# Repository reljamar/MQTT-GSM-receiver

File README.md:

# MQTT-GSM-receiver
_A basic IoT device that connects to a mobile network and activates an output pin based on an MQTT message. The project is a work in progress_

## Purpose
This project is intended to be a basis of operation for a vast number of possible uses. The microcontroller connects to an MQTT topic and checks for key messages. When the appropriate message is received, an output pin is activated. With aditional periferal hardware, the device can be adapted to do various tasks. An important detail about the project is that unlike most IoT devices that connect via WiFi, this one connects via the mobile network, allowing it to be placed outside the range of WiFi networks: backyards, open fields, practically anywhere. The project also serves to prived an introduction to RF connectivity.

## Description
A device that uses the STM32L476RET6 microcontroller. The microcontroller communicates with a Quectel BC660K-GL GSM module using AT commands. The device subsribes to a topic on a server set up by the user, and an mobile phone application can send messages to that topic, which trigger the IoT device to activate an output signal. The device features a SIM card, EEPROM, and an input/ouput interface. Cybersecurity is of crucial importance for this application, however it is far from being developed at the time of writing. Currently an external antenna is used, but future iterations may include a built-in PCB antenna.

## Overview
- Quectel CB660K-GL GMS module for connectivity
- EEPROM for cybersecurity credentials
- Basis for projects with a well-defined use case

## System architecture
### Microcontroller
The system is based on an STM32L476RET6. They are readily available and powerful enough for encryption tasks. The microcontroller communicates vie UART using AT commands with the GSM module
### GSM Module
The module is Quectel's BC660K-GL. This is one of the cheapest GMS modules available, and even they are sometimes difficult to get by. The module is very easy to use with the AT commands, which makes development much faster. An important note is the antenna design, which is currently a weak spot in the project. Occasionally, the device simply loses its connection with the network. The module requires a SIM card. Some carriers offer IoT-specific services, which come with only data at a very slow rate, but are also very cheap on a monthly level.
### Antenna
The antenna is the weak link, and much care is needed when routing the antenna signal, even if an external antenna is used. Impedance control is very important here.

## Firmware
### Implemented features
- [x] Connecting to a GSM network
- [x] Subscribing to a topic
- [x] Error handling - lost connection triggers a reconnection attempt
- [x] Output pin control based on MQTT messages
### Planned features
- [ ] Cybersecurity
- [ ] Reporting/check-in feature
- [ ] Sending data from the input to the server

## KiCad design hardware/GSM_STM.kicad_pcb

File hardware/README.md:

This folder contains all of the hardware project files.
There is only one schematic page containing all the functions.
A BOM is attached since the antenna is not visible in the PCB project.

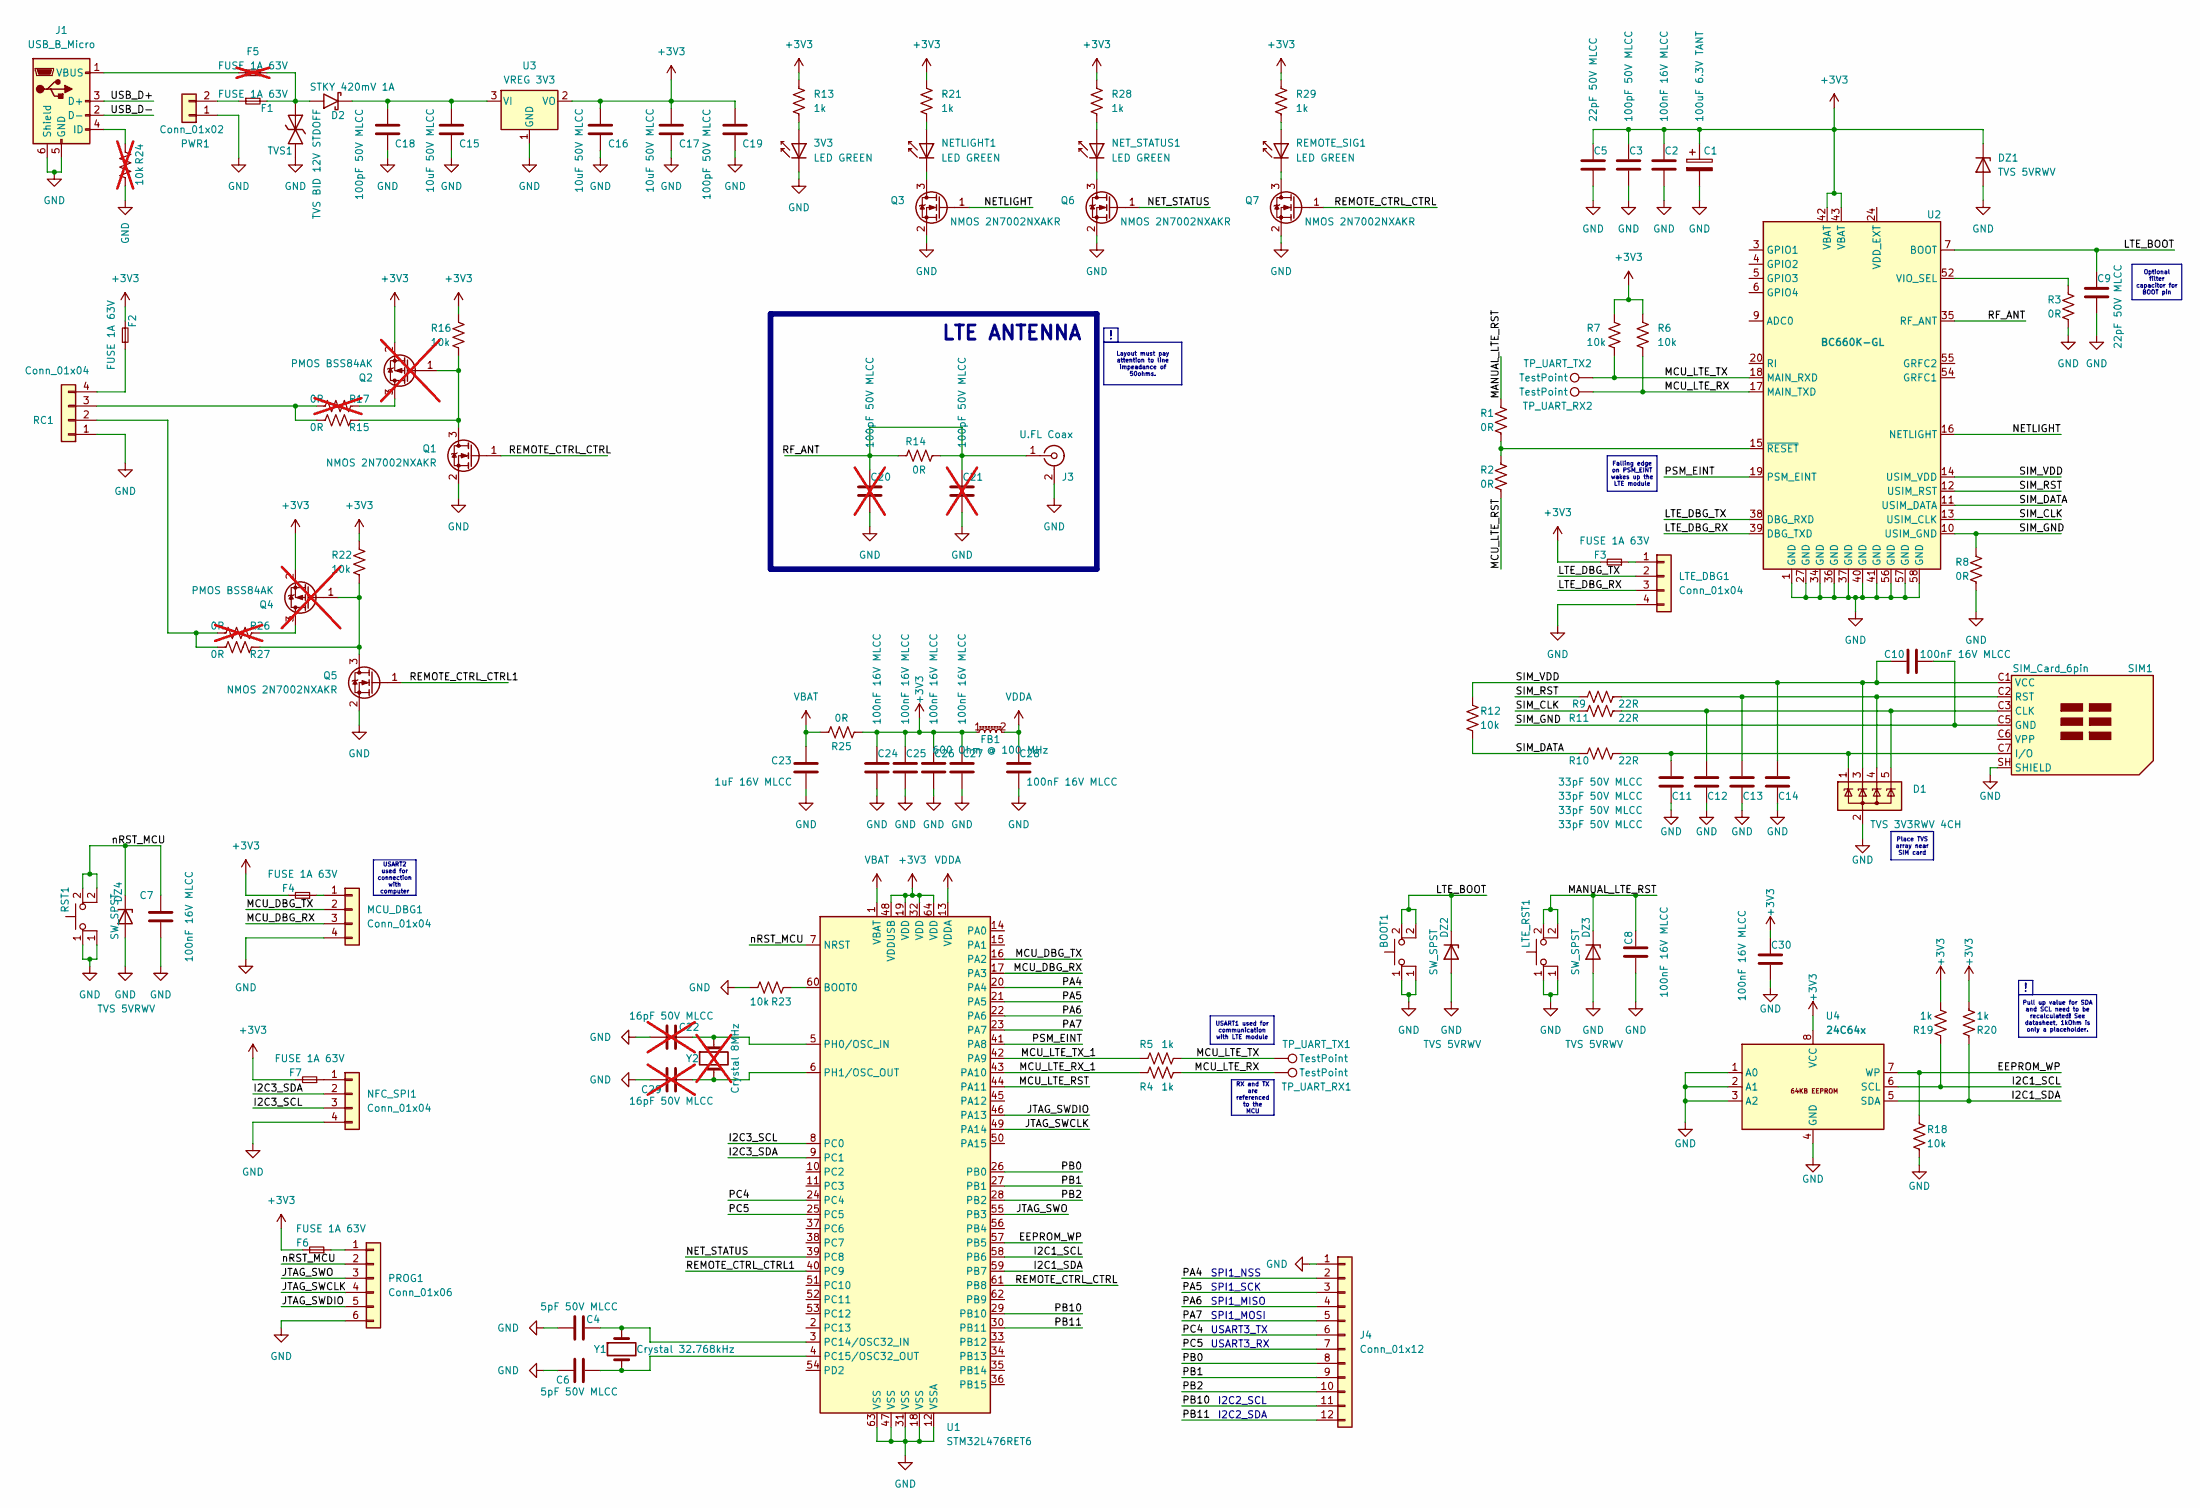
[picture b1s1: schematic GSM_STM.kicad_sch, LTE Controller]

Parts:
3V3: LED GREEN; LED_0603_1608Metric; Forward Voltage 2V; Manufacturer Part Number 150060VS75000
BOOT1: SW_SPST; SW_SPST_PTS645; Contact Rating 50mA @ 12V; Manufacturer Part Number PTS645SL43SMTR92 LFS
C1: 100uF 6.3V TANT; CP_EIA-3528-15_AVX-H; Tolerance 10%; Rated Voltage 6.3V; Manufacturer Part Number TPSB107K006R0250
C2, C7, C8, C10, C24, C25, C26, C27, C28, C30: 100nF 16V MLCC; C_0603_1608Metric; Tolerance 10%; Rated Voltage 16V; Manufacturer Part Number CL10B104KO8NNNC
C3, C18, C19: 100pF 50V MLCC; C_0603_1608Metric; Tolerance 5%; Rated Voltage 50V; Manufacturer Part Number CC0603JRNPO9BN101
C4, C6: 5pF 50V MLCC; C_0402_1005Metric; Tolerance ±0.1pF; Rated Voltage 50V; Manufacturer Part Number CC0402BRNPO9BN5R0
C5, C9: 22pF 50V MLCC; C_0603_1608Metric; Tolerance 5%; Rated Voltage 50V; Manufacturer Part Number CC0603JRNPO9BN220
C11, C12, C13, C14: 33pF 50V MLCC; C_0603_1608Metric; Tolerance 5%; Rated Voltage 50V; Manufacturer Part Number CL10C330JB8NNNC
C15, C16, C17: 10uF 50V MLCC; C_1206_3216Metric; Tolerance 10%; Rated Voltage 50V; Manufacturer Part Number CL31B106KBHNNNE
C20, C21: 100pF 50V MLCC; C_0603_1608Metric; Tolerance 5%; Rated Voltage 50V; Manufacturer Part Number CC0603JRNPO9BN101; not fitted
C22, C29: 16pF 50V MLCC; C_0402_1005Metric; Tolerance ±1%; Rated Voltage 50V; Manufacturer Part Number GJM1555C1H160FB01J; not fitted
C23: 1uF 16V MLCC; C_0603_1608Metric; Tolerance 10%; Rated Voltage 16V; Manufacturer Part Number CC0603KRX7R7BB105
D1: TVS 3V3RWV 4CH; SOT-665; Clamping Voltage 12V @ Ipp = 3A; Manufacturer Part Number PESD3V3L4UW
D2: STKY 420mV 1A; D_SMA; Forward Voltage 420mV @ 1A; Manufacturer Part Number SS12L_R1_00001
DZ1, DZ2, DZ3, DZ4: TVS 5VRWV; D_SOD-923; Clamping Voltage 12.3V; Manufacturer Part Number ESD9X5.0ST5G
F1, F2, F3, F4, F6, F7: FUSE 1A 63V; Fuse_1206_3216Metric; Current Rating 1A; Voltage Rating 63V; Manufacturer Part Number 0685T1000-01
F5: FUSE 1A 63V; Fuse_1206_3216Metric; Current Rating 1A; Voltage Rating 63V; Manufacturer Part Number 0685T1000-01; not fitted
FB1: 600 Ohm @ 100 MHz; L_0603_1608Metric; Current Rating (Max) 300mA; Manufacturer Part Number BBBK00160808601Y00
J1: USB_B_Micro; USB_Micro-B_Amphenol_10118194_Horizontal; Manufacturer Part Number 10118194-0001LF
J3: U.FL Coax; U.FL_Molex_MCRF_73412-0110_Vertical; Manufacturer Part Number CONMHF1-SMD-T
J4: Conn_01x12; PinHeader_1x12_P2.54mm_Vertical
LTE_DBG1: Conn_01x04; Molex_KK-254_AE-6410-04A_1x04_P2.54mm_Vertical
LTE_RST1: SW_SPST; SW_SPST_PTS645; Contact Rating 50mA @ 12V; Manufacturer Part Number PTS645SL43SMTR92 LFS
MCU_DBG1: Conn_01x04; Molex_KK-254_AE-6410-04A_1x04_P2.54mm_Vertical
NETLIGHT1: LED GREEN; LED_0603_1608Metric; Forward Voltage 2V; Manufacturer Part Number 150060VS75000
NET_STATUS1: LED GREEN; LED_0603_1608Metric; Forward Voltage 2V; Manufacturer Part Number 150060VS75000
NFC_SPI1: Conn_01x04; Molex_KK-254_AE-6410-04A_1x04_P2.54mm_Vertical
PROG1: Conn_01x06; Molex_KK-254_AE-6410-06A_1x06_P2.54mm_Vertical
PWR1: Conn_01x02; Molex_KK-254_AE-6410-02A_1x02_P2.54mm_Vertical
Q1, Q3, Q5, Q6, Q7: NMOS 2N7002NXAKR; SOT-23-3; Manufacturer Part Number 2N7002NXAKR
Q2, Q4: PMOS BSS84AK; SOT-23-3; Manufacturer Part Number BSS84AK; not fitted
R1, R2, R3, R8, R14, R15, R25, R27: 0R; R_0603_1608Metric; Tolerance Jumper; Power Rating 100mW; Manufacturer Part Number ERJ-3GEY0R00V
R4, R5, R13, R19, R20, R21, R28, R29: 1k; R_0603_1608Metric; Tolerance 1%; Power Rating 100mW; Manufacturer Part Number ERJ-3EKF1001V
R6, R7, R12, R16, R18, R22, R23: 10k; R_0603_1608Metric; Tolerance 1%; Power Rating 100mW; Manufacturer Part Number ERJ-3EKF1002V
R9, R10, R11: 22R; R_0603_1608Metric; Tolerance 1%; Power Rating 100mW; Manufacturer Part Number RC0603FR-0722RL
R17, R26: 0R; R_0603_1608Metric; Tolerance Jumper; Power Rating 100mW; Manufacturer Part Number ERJ-3GEY0R00V; not fitted
R24: 10k; R_0603_1608Metric; Tolerance 1%; Power Rating 100mW; Manufacturer Part Number ERJ-3EKF1002V; not fitted
RC1: Conn_01x04; Molex_KK-254_AE-6410-04A_1x04_P2.54mm_Vertical
REMOTE_SIG1: LED GREEN; LED_0603_1608Metric; Forward Voltage 2V; Manufacturer Part Number 150060VS75000
RST1: SW_SPST; SW_SPST_PTS645; Contact Rating 50mA @ 12V; Manufacturer Part Number PTS645SL43SMTR92 LFS
SIM1: SIM_Card_6pin; CUI_MICRO_SIM; Manufacturer Part Number MSIM-10-B
TP_UART_RX1, TP_UART_RX2: TestPoint; TestPoint_Pad_1.0x1.0mm
TP_UART_TX1, TP_UART_TX2: TestPoint; TestPoint_Pad_1.0x1.0mm
TVS1: TVS BID 12V STDOFF; D_SMB; Breakdown Voltage 13.3V; Clamping Voltage 19V; Manufacturer Part Number P6SMBJ12CA_R1_00001
U1: STM32L476RET6; LQFP-64_10x10mm_P0.5mm; Manufacturer Part Number STM32L476RET6TR
U2: BC660K-GL; Quectel_BC66; Manufacturer Part Number BC660K-GL
U3: VREG 3V3; SOT-223-3_TabPin2; Output Voltage 3.3V; Dropout Voltage 1.2V; Manufacturer Part Number AZ1117IH-3.3TRG1
U4: 24C64x; SOIC-8_3.9x4.9mm_P1.27mm; Manufacturer Part Number AT24C64D-SSHM-T
Y1: Crystal 32.768kHz; Crystal_C38-LF_D3.0mm_L8.0mm_Horizontal; Frequency Tolerance ±20ppm; Manufacturer Part Number 32.768K12.5P2/DT38
Y2: Crystal 8MHz; Crystal_SMD_HC49-SD; Frequency Tolerance ±30ppm; Manufacturer Part Number ATS080BSM-1E; not fitted

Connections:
+3V3: C1.1, C2.1, C3.1, C5.1, C16.1, C17.1, C19.2, C24.1, C25.1, C26.1, C27.1, C30.1, DZ1.1 (K), F2.2, F3.2, F4.2, F6.2, F7.2, FB1.1, Q2.2 (S), Q4.2 (S), R6.1, R7.1, R13.1, R16.1, R19.1, R20.1, R21.1, R22.1, R25.2, R28.1, R29.1, U1.19 (VDD), U1.32 (VDD), U1.48 (VDDUSB), U1.64 (VDD), U2.42 (VBAT), U2.43 (VBAT), U3.2 (VO), U4.8 (VCC)
/EEPROM_WP: R18.1, U1.57 (PB5), U4.7 (WP)
/I2C1_SCL: R19.2, U1.58 (PB6), U4.6 (SCL)
/I2C1_SDA: R20.2, U1.59 (PB7), U4.5 (SDA)
/I2C3_SCL: NFC_SPI1.3, U1.8 (PC0)
/I2C3_SDA: NFC_SPI1.2, U1.9 (PC1)
/JTAG_SWCLK: PROG1.4, U1.49 (PA14)
/JTAG_SWDIO: PROG1.5, U1.46 (PA13)
/JTAG_SWO: PROG1.3, U1.55 (PB3)
/LTE_BOOT: BOOT1.2, C9.1, DZ2.1 (K), U2.7 (BOOT)
/LTE_DBG_RX: LTE_DBG1.3, U2.39 (DBG_TXD)
/LTE_DBG_TX: LTE_DBG1.2, U2.38 (DBG_RXD)
/MANUAL_LTE_RST: C8.2, DZ3.1 (K), LTE_RST1.2, R1.1
/MCU_DBG_RX: MCU_DBG1.3, U1.17 (PA3)
/MCU_DBG_TX: MCU_DBG1.2, U1.16 (PA2)
/MCU_LTE_RST: R2.2, U1.44 (PA11)
/MCU_LTE_RX: R4.1, R6.2, TP_UART_RX1.1, TP_UART_RX2.1, U2.17 (MAIN_TXD)
/MCU_LTE_RX_1: R4.2, U1.43 (PA10)
/MCU_LTE_TX: R5.1, R7.2, TP_UART_TX1.1, TP_UART_TX2.1, U2.18 (MAIN_RXD)
/MCU_LTE_TX_1: R5.2, U1.42 (PA9)
/NETLIGHT: Q3.1 (G), U2.16 (NETLIGHT)
/NET_STATUS: Q6.1 (G), U1.39 (PC8)
/PA4: J4.2, U1.20 (PA4)
/PA5: J4.3, U1.21 (PA5)
/PA6: J4.4, U1.22 (PA6)
/PA7: J4.5, U1.23 (PA7)
/PB0: J4.8, U1.26 (PB0)
/PB1: J4.9, U1.27 (PB1)
/PB2: J4.10, U1.28 (PB2)
/PB10: J4.11, U1.29 (PB10)
/PB11: J4.12, U1.30 (PB11)
/PC4: J4.6, U1.24 (PC4)
/PC5: J4.7, U1.25 (PC5)
/PSM_EINT: U1.41 (PA8), U2.19 (PSM_EINT)
/REMOTE_CTRL_CTRL: Q1.1 (G), Q7.1 (G), U1.61 (PB8)
/REMOTE_CTRL_CTRL1: Q5.1 (G), U1.40 (PC9)
/RF_ANT: C20.1, C21.1, J3.1 (In), R14.1, R14.2, U2.35 (RF_ANT)
/SIM_CLK: R11.1, U2.13 (USIM_CLK)
/SIM_DATA: R10.1, R12.2, U2.11 (USIM_DATA)
/SIM_GND: C10.2, R8.1, SIM1.C5 (GND), U2.10 (USIM_GND)
/SIM_RST: R9.1, U2.12 (USIM_RST)
/SIM_VDD: C10.1, C14.1, D1.3 (K), R12.1, SIM1.C1 (VCC), U2.14 (USIM_VDD)
/USB_D+: J1.3 (D+)
/USB_D-: J1.2 (D-)
/nRST_MCU: C7.2, DZ4.1 (K), PROG1.2, RST1.2, U1.7 (NRST)
GND: 3V3.1 (K), BOOT1.1, C1.2, C2.2, C3.2, C4.1, C5.2, C6.1, C7.1, C8.1, C9.2, C11.2, C12.2, C13.2, C14.2, C15.2, C16.2, C17.2, C18.1, C19.1, C20.2, C21.2, C22.1, C23.2, C24.2, C25.2, C26.2, C27.2, C28.2, C29.1, C30.2, D1.2 (A), DZ1.2 (A), DZ2.2 (A), DZ3.2 (A), DZ4.2 (A), J1.5 (GND), J1.6 (Shield), J3.2 (Ext), J4.1, LTE_DBG1.4, LTE_RST1.1, MCU_DBG1.4, NFC_SPI1.4, PROG1.6, PWR1.1, Q1.2 (S), Q3.2 (S), Q5.2 (S), Q6.2 (S), Q7.2 (S), R3.2, R8.2, R18.2, R23.2, R24.2, RC1.1, RST1.1, SIM1.SH (SHIELD), TVS1.1 (K), U1.12 (VSSA), U1.18 (VSS), U1.31 (VSS), U1.47 (VSS), U1.63 (VSS), U2.1 (GND), U2.27 (GND), U2.34 (GND), U2.36 (GND), U2.37 (GND), U2.40 (GND), U2.41 (GND), U2.56 (GND), U2.57 (GND), U2.58 (GND), U3.1 (GND), U4.1 (A0), U4.2 (A1), U4.3 (A2), U4.4 (GND)
unnamed: 3V3.2 (A), R13.2
unnamed: D2.2 (A), F1.2, F5.2, TVS1.2 (A)
unnamed: C15.1, C18.2, D2.1 (K), U3.3 (VI)
unnamed: J1.4 (ID), R24.1
unnamed: F5.1, J1.1 (VBUS)
unnamed: F3.1, LTE_DBG1.1
unnamed: F4.1, MCU_DBG1.1
unnamed: NETLIGHT1.2 (A), R21.2
unnamed: NETLIGHT1.1 (K), Q3.3 (D)
unnamed: NET_STATUS1.2 (A), R28.2
unnamed: NET_STATUS1.1 (K), Q6.3 (D)
unnamed: F7.1, NFC_SPI1.1
unnamed: F6.1, PROG1.1
unnamed: F1.1, PWR1.2
unnamed: Q1.3 (D), Q2.1 (G), R15.2, R16.2
unnamed: Q2.3 (D), R17.2
unnamed: Q4.3 (D), R26.2
unnamed: Q4.1 (G), Q5.3 (D), R22.2, R27.2
unnamed: Q7.3 (D), REMOTE_SIG1.1 (K)
unnamed: R26.1, R27.1, RC1.2
unnamed: R15.1, R17.1, RC1.3
unnamed: F2.1, RC1.4
unnamed: R29.2, REMOTE_SIG1.2 (A)
unnamed: C12.1, D1.5 (K), R11.2, SIM1.C3 (CLK)
unnamed: C11.1, D1.1 (K), R10.2, SIM1.C7 (I/O)
unnamed: C13.1, D1.4 (K), R9.2, SIM1.C2 (RST)
unnamed: R23.1, U1.60 (BOOT0)
unnamed: C4.2, U1.3 (PC14/OSC32_IN), Y1.1
unnamed: C6.2, U1.4 (PC15/OSC32_OUT), Y1.2
unnamed: C22.2, U1.5 (PH0/OSC_IN), Y2.1
unnamed: C29.2, U1.6 (PH1/OSC_OUT), Y2.2
unnamed: R3.1, U2.52 (VIO_SEL)
unnamed: R1.2, R2.1, U2.15 (~RESET)
VBAT: C23.1, R25.1, U1.1 (VBAT)
VDDA: C28.1, FB1.2, U1.13 (VDDA)

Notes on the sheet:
Layout must pay attention to line impeadance of 50ohms.
Pull up value for SDA and SCL need to be recalculated! See datasheet, 1kOhm is only a placeholder.
USART2 used for connection with computer
Optional filter capacitor for BOOT pin
Place TVS array near SIM card
RX and TX are referenced to the MCU
Falling edge on PSM_EINT wakes up the LTE module
USART1 used for communication with LTE module
USART3_RX
USART3_TX
SPI1_MOSI
SPI1_NSS
SPI1_SCK
SPI1_MISO
I2C2_SCL
I2C2_SDA
LTE ANTENNA

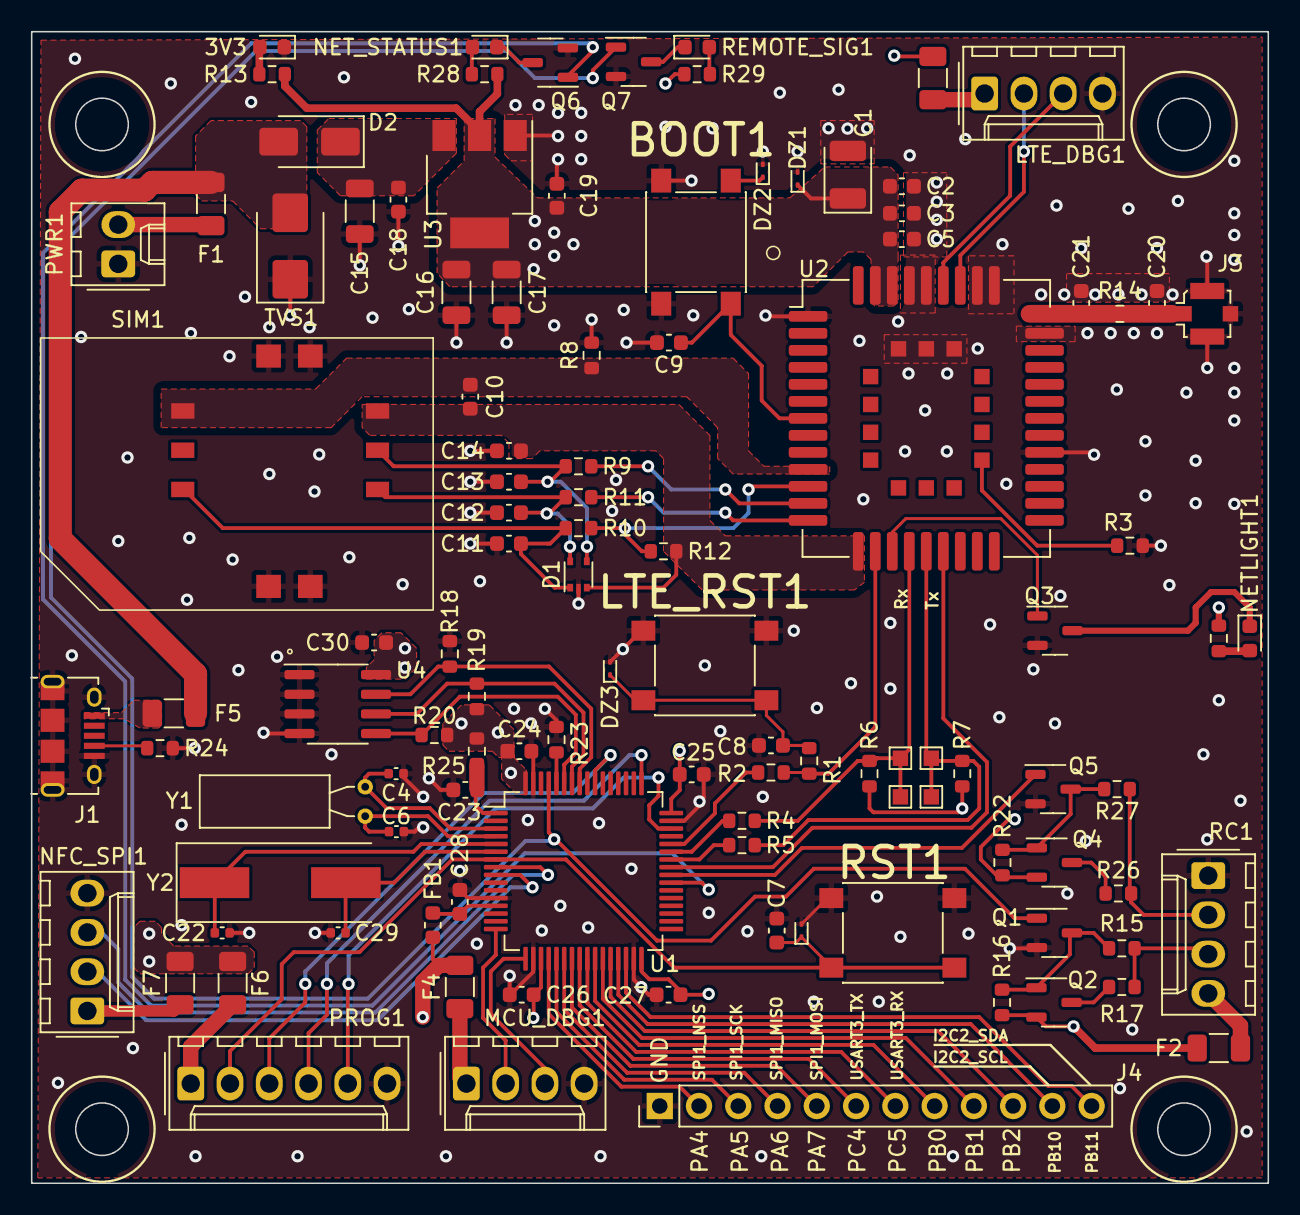
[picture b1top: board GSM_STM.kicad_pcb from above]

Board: 4 copper layers, 80.0 x 74.5 mm, 108 parts (0 on the bottom side), 79 nets.

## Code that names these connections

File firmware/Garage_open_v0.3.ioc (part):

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Mcu.Name=STM32L476R(C-E-G)Tx
Mcu.Package=LQFP64
Mcu.UserName=STM32L476RGTx
PA10.Mode=Asynchronous
PA10.Signal=USART1_RX
PA11.GPIOParameters=PinState,GPIO_PuPd
PA11.GPIO_PuPd=GPIO_PULLUP
PA11.PinState=GPIO_PIN_SET
PA11.Signal=GPIO_Output
PA13\ (JTMS-SWDIO).GPIOParameters=GPIO_Label
PA13\ (JTMS-SWDIO).GPIO_Label=TMS
PA13\ (JTMS-SWDIO).Mode=Serial_Wire
PA13\ (JTMS-SWDIO).Signal=SYS_JTMS-SWDIO
PA14\ (JTCK-SWCLK).GPIOParameters=GPIO_Label
PA14\ (JTCK-SWCLK).GPIO_Label=TCK
PA14\ (JTCK-SWCLK).Mode=Serial_Wire
PA14\ (JTCK-SWCLK).Signal=SYS_JTCK-SWCLK
PA2.GPIOParameters=GPIO_Speed,GPIO_PuPd,GPIO_Label,GPIO_Mode
PA2.GPIO_Label=USART_TX
PA2.GPIO_Mode=GPIO_MODE_AF_PP
PA2.GPIO_PuPd=GPIO_NOPULL
PA2.GPIO_Speed=GPIO_SPEED_FREQ_VERY_HIGH
PA2.Mode=Asynchronous
PA2.Signal=USART2_TX
PA3.GPIOParameters=GPIO_Speed,GPIO_PuPd,GPIO_Label,GPIO_Mode
PA3.GPIO_Label=USART_RX
PA3.GPIO_Mode=GPIO_MODE_AF_PP
PA3.GPIO_PuPd=GPIO_NOPULL
PA3.GPIO_Speed=GPIO_SPEED_FREQ_VERY_HIGH
PA3.Mode=Asynchronous
PA3.Signal=USART2_RX
PA5.GPIOParameters=GPIO_Speed,GPIO_PuPd,GPIO_Label,GPIO_ModeDefaultOutputPP
PA5.GPIO_Label=LD2 [green Led]
PA5.GPIO_ModeDefaultOutputPP=GPIO_MODE_OUTPUT_PP
PA5.GPIO_PuPd=GPIO_NOPULL
PA5.GPIO_Speed=GPIO_SPEED_FREQ_LOW
PA5.Signal=GPIO_Output
PA9.Mode=Asynchronous
PA9.Signal=USART1_TX
PB3\ (JTDO-TRACESWO).GPIOParameters=GPIO_Label
PB3\ (JTDO-TRACESWO).GPIO_Label=SWO
PB3\ (JTDO-TRACESWO).Signal=SYS_JTDO-SWO
PB8.GPIOParameters=GPIO_PuPd
PB8.GPIO_PuPd=GPIO_PULLDOWN
PB8.Signal=GPIO_Output
PC13.GPIOParameters=GPIO_PuPd,GPIO_Label,GPIO_ModeDefaultEXTI
PC13.GPIO_Label=B1 [Blue PushButton]
PC13.GPIO_ModeDefaultEXTI=GPIO_MODE_IT_FALLING
PC13.GPIO_PuPd=GPIO_NOPULL
PC13.Signal=GPXTI13
PC14-OSC32_IN\ (PC14).Mode=LSE-External-Oscillator
PC14-OSC32_IN\ (PC14).Signal=RCC_OSC32_IN
PC15-OSC32_OUT\ (PC15).Mode=LSE-External-Oscillator
PC15-OSC32_OUT\ (PC15).Signal=RCC_OSC32_OUT
PH0-OSC_IN\ (PH0).Signal=RCC_OSC_IN
PH1-OSC_OUT\ (PH1).Signal=RCC_OSC_OUT
RCC.HSE_VALUE=8000000
RCC.SYSCLKFreq_VALUE=80000000
RCC.SYSCLKSource=RCC_SYSCLKSOURCE_PLLCLK
board=NUCLEO-L476RG
boardIOC=true
